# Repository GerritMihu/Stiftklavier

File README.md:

# Stiftklavier / Stylophone

**Ein Open-Source-Lehrprojekt für Mechatronik, Elektronik und Musik** – ideal für Workshops, Schulen und Maker.

*(Abb.: Fertiger Aufbau mit 3D-gedrucktem Gehäuse)*

---
## 🎯 Projektziel
Das Stiftklavier ist ein **praktisches Lehrmittel**, um:
✅ **Löten und Schaltungen** zu üben (Widerstände, ICs, Transistoren)
✅ **Grundlagen der Tonerzeugung** zu verstehen (Oszillatoren, Filter)
✅ **Mechatronik** zu verbinden (Elektronik + 3D-Druck + Mechanik)
✅ **Kreativität** zu fördern (individuelle Gehäuse, Sound-Experimente)

**Zielgruppe**: Student:innen, Lehrende, Elektronik-Enthusiast:innen

---
## 📦 Inhalte dieses Repos
| Ordner/Datei          | Beschreibung                                  |
|-----------------------|-----------------------------------------------|
| [`3D/`](3D/)          | 3D-Modelle für Gehäuse (STL, FreeCAD)         |
| [`bom/`](bom/)        | Stücklisten (BOM) und Bestelllinks           |
| [`cam/`](cam/)        | **Automatisch generierte KiBot-Exporte** (PDF/PNG/3D) |
| [`Stylophone Documentation.md`](Stylophone%20Documentation.md) | **Detaillierte Aufbauanleitung** 🔗 |
| [`Stylophon_1.kicad_sch`](Stylophon_1.kicad_sch) | KiCad-Schaltplan und Platinenlayout |

---
## 🛠️ Loslegen
### 1. Material besorgen
- [Stückliste (BOM)](bom/) mit empfohlenen Händlern.
- **Werkzeuge**: Lötkolben, Multimeter, 3D-Drucker (optional).

### 2. Aufbauen
→ **[Schritt-für-Schritt-Anleitung](Stylophone%20Documentation.md)**

### 3. Erweitern
- Experimentiere mit **anderen Widerständen** für neue Tonleitern.
- Baue ein **MIDI-Interface** ein (Code-Beispiele folgen).

---
## 🔧 CI/CD mit KiBot (KiCad 10 Docker)
Dieses Repo nutzt **[KiBot](https://github.com/INTI-CMNB/KiBot)** in einem **vorkonfigurierten Docker-Container für KiCad 10**, um automatisch:
- **Schaltpläne als PDF** zu exportieren
- **Platinen-Layouts als PNG** zu rendern
- **3D-Ansichten** der Platine zu generieren

👉 **Ergebnisse**: Siehe [`cam/`](cam/)-Ordner (automatisch aktualisiert bei Pushs).

---
## 🤝 Mitwirken
- **Fehler gefunden?** → [Issue erstellen](https://github.com/GerritMihu/Stiftklavier/issues)
- **Verbesserungen?** → Pull Requests willkommen!
- **Fragen?** → Diskussionsbereich nutzen.

---
## 📄 Lizenz
[MIT](LICENSE) – Nutze, modifiziere und teile das Projekt frei!

<!-- KiBot Docker Pipeline Test Trigger: $(date +%s) -->

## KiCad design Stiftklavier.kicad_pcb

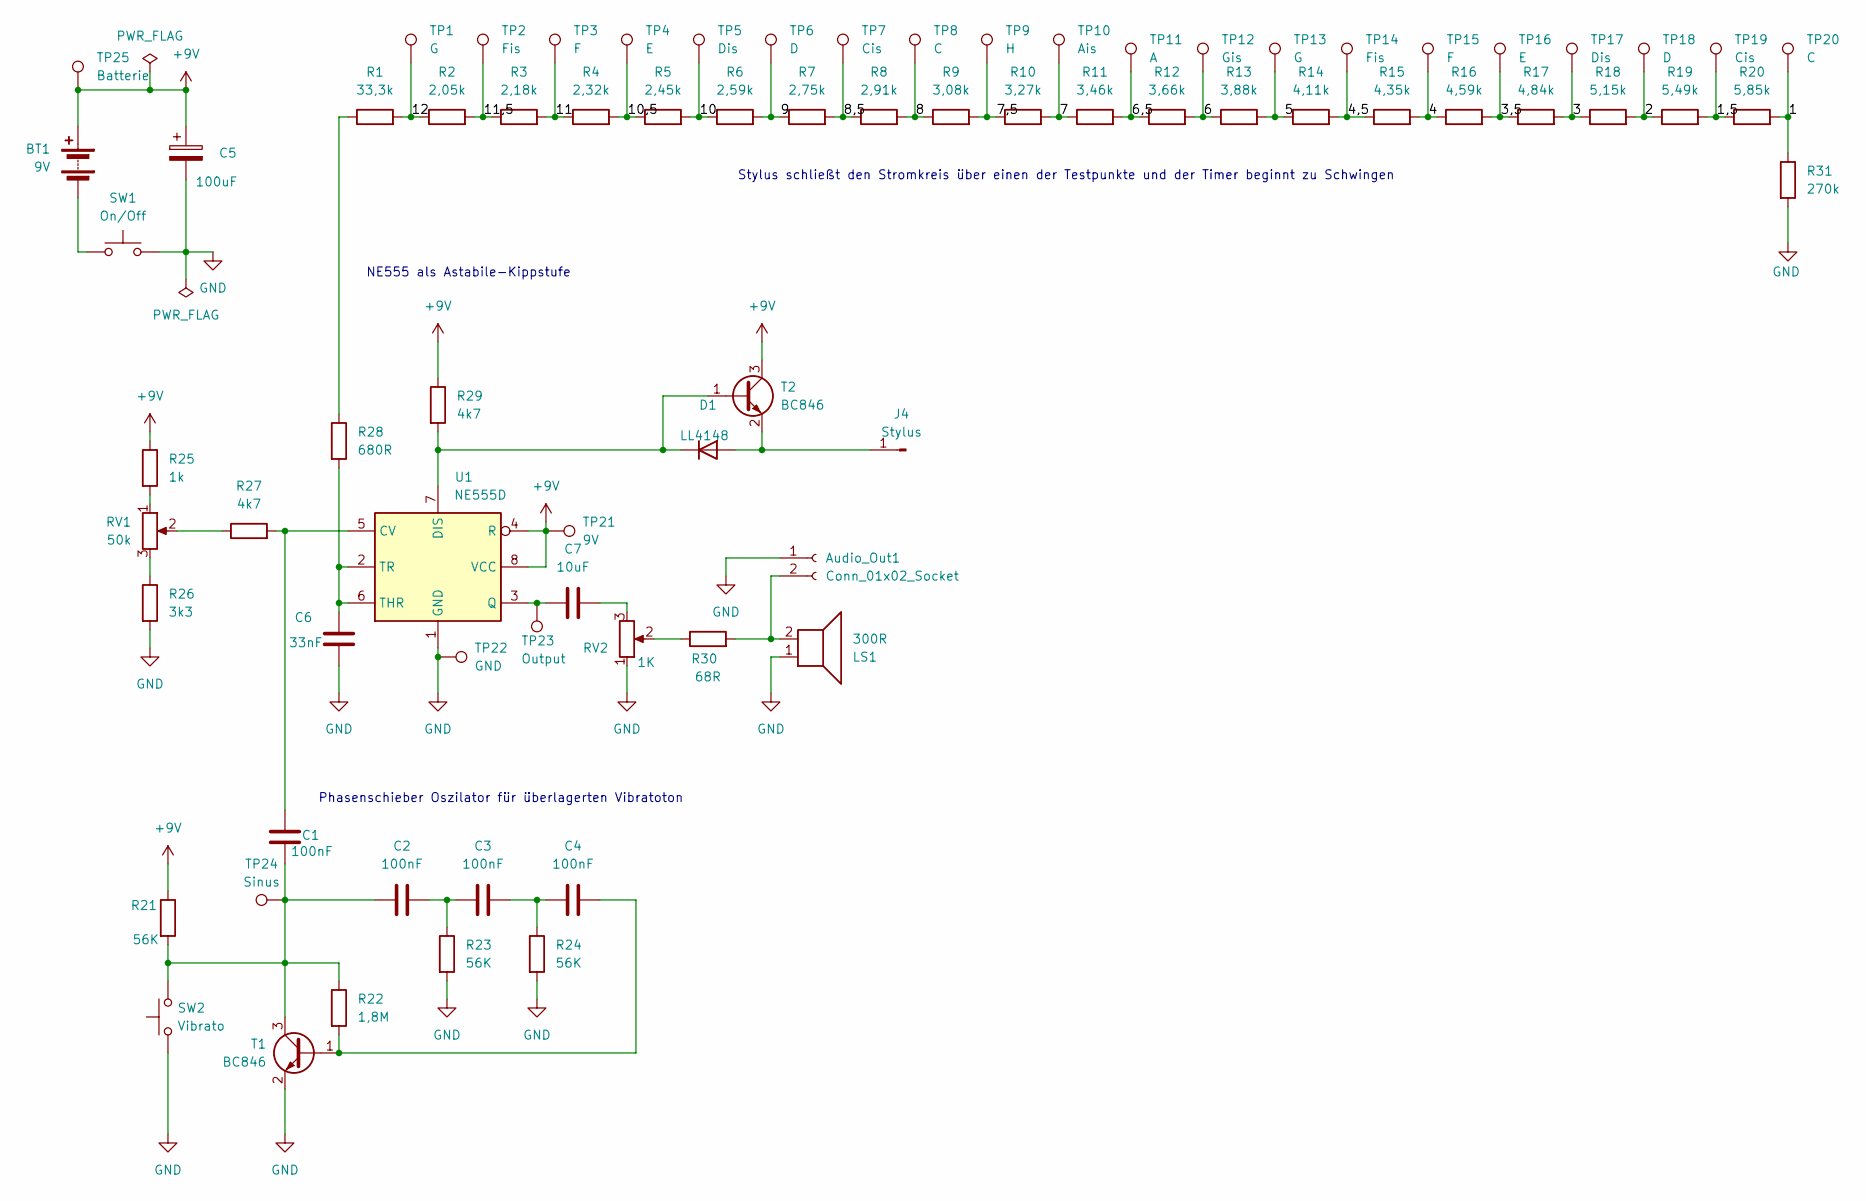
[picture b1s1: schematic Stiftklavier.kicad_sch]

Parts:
Audio_Out1: Conn_01x02_Socket; PinSocket_1x02_P2.00mm_Vertical
BT1: 9V; PinHeader_1x02_P2.54mm_Vertical
C1, C2, C3, C4: 100nF; C_0805_2012Metric_Pad1.18x1.45mm_HandSolder
C5: 100uF; CP_Elec_6.3x7.7
C6: 33nF; C_0805_2012Metric_Pad1.18x1.45mm_HandSolder
C7: 10uF; C_0805_2012Metric_Pad1.18x1.45mm_HandSolder
D1: LL4148; D_MiniMELF
J4: Stylus; PinHeader_1x01_P2.00mm_Vertical
LS1: 300R; PinSocket_1x02_P2.00mm_Vertical
R1: 33,3k; R_1206_3216Metric_Pad1.30x1.75mm_HandSolder
R2: 2,05k; R_1206_3216Metric_Pad1.30x1.75mm_HandSolder
R3: 2,18k; R_1206_3216Metric_Pad1.30x1.75mm_HandSolder
R4: 2,32k; R_1206_3216Metric_Pad1.30x1.75mm_HandSolder
R5: 2,45k; R_1206_3216Metric_Pad1.30x1.75mm_HandSolder
R6: 2,59k; R_1206_3216Metric_Pad1.30x1.75mm_HandSolder
R7: 2,75k; R_1206_3216Metric_Pad1.30x1.75mm_HandSolder
R8: 2,91k; R_1206_3216Metric_Pad1.30x1.75mm_HandSolder
R9: 3,08k; R_1206_3216Metric_Pad1.30x1.75mm_HandSolder
R10: 3,27k; R_1206_3216Metric_Pad1.30x1.75mm_HandSolder
R11: 3,46k; R_1206_3216Metric_Pad1.30x1.75mm_HandSolder
R12: 3,66k; R_1206_3216Metric_Pad1.30x1.75mm_HandSolder
R13: 3,88k; R_1206_3216Metric_Pad1.30x1.75mm_HandSolder
R14: 4,11k; R_1206_3216Metric_Pad1.30x1.75mm_HandSolder
R15: 4,35k; R_1206_3216Metric_Pad1.30x1.75mm_HandSolder
R16: 4,59k; R_1206_3216Metric_Pad1.30x1.75mm_HandSolder
R17: 4,84k; R_1206_3216Metric_Pad1.30x1.75mm_HandSolder
R18: 5,15k; R_1206_3216Metric_Pad1.30x1.75mm_HandSolder
R19: 5,49k; R_1206_3216Metric_Pad1.30x1.75mm_HandSolder
R20: 5,85k; R_1206_3216Metric_Pad1.30x1.75mm_HandSolder
R21, R23, R24: 56K; R_1206_3216Metric_Pad1.30x1.75mm_HandSolder
R22: 1,8M; R_1206_3216Metric_Pad1.30x1.75mm_HandSolder
R25: 1k; R_1206_3216Metric_Pad1.30x1.75mm_HandSolder
R26: 3k3; R_1206_3216Metric_Pad1.30x1.75mm_HandSolder
R27, R29: 4k7; R_1206_3216Metric_Pad1.30x1.75mm_HandSolder
R28: 680R; R_1206_3216Metric_Pad1.30x1.75mm_HandSolder
R30: 68R; R_1206_3216Metric_Pad1.30x1.75mm_HandSolder
R31: 270k; R_1206_3216Metric_Pad1.30x1.75mm_HandSolder
RV1: 50k; PinSocket_1x03_P2.00mm_Vertical
RV2: 1K; PinSocket_1x03_P2.00mm_Vertical
SW1: On/Off; Nidec_Copal_SH-7040B
SW2: Vibrato; Nidec_Copal_SH-7040B
T1, T2: BC846; SOT-23
TP1, TP13: G; Keypad_Right
TP2, TP14: Fis; Keypad_Small
TP3, TP15: F; Keypad_Small
TP4, TP16: E; Keypad_Small
TP5, TP17: Dis; Keypad_Left
TP6, TP18: D; Keypad_Right
TP7, TP19: Cis; Keypad_Small
TP8: C; Keypad_Small
TP9: H; Keypad_Small
TP10: Ais; Keypad_Small
TP11: A; Keypad_Small
TP12: Gis; Keypad_Left
TP20: C; Keypad_Left
TP21: 9V; TestPoint_Pad_D1.5mm
TP22: GND; TestPoint_Pad_D1.5mm
TP23: Output; TestPoint_Pad_D1.5mm
TP24: Sinus; TestPoint_Pad_D1.5mm
TP25: Batterie; TestPoint_Pad_D1.5mm
U1: NE555D; SOIC-8_3.9x4.9mm_P1.27mm

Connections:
+9V: BT1.1 (+), C5.1, R21.1, R25.1, R29.1, T2.3 (C), TP21.1, TP25.1, U1.4 (R), U1.8 (VCC)
/1: R20.2, R31.1, TP20.1
/1,5: R19.2, R20.1, TP19.1
/2: R18.2, R19.1, TP18.1
/3: R17.2, R18.1, TP17.1
/3,5: R16.2, R17.1, TP16.1
/4: R15.2, R16.1, TP15.1
/4,5: R14.2, R15.1, TP14.1
/5: R13.2, R14.1, TP13.1
/6: R12.2, R13.1, TP12.1
/6,5: R11.2, R12.1, TP11.1
/7: R10.2, R11.1, TP10.1
/7,5: R9.2, R10.1, TP9.1
/8: R8.2, R9.1, TP8.1
/8,5: R7.2, R8.1, TP7.1
/9: R6.2, R7.1, TP6.1
/10: R5.2, R6.1, TP5.1
/10,5: R4.2, R5.1, TP4.1
/11: R3.2, R4.1, TP3.1
/11,5: R2.2, R3.1, TP2.1
/12: R1.2, R2.1, TP1.1
GND: Audio_Out1.1, C5.2, C6.2, LS1.1, R23.2, R24.2, R26.2, R31.2, RV2.1, SW1.2, SW2.1, T1.2 (E), TP22.1, U1.1 (GND)
unnamed: Audio_Out1.2, LS1.2, R30.2
unnamed: BT1.2 (-), SW1.1
unnamed: C2.1, C3.2, R23.1
unnamed: C3.1, C4.2, R24.1
unnamed: C7.2, RV2.3
unnamed: D1.2 (A), J4.1, T2.2 (E)
unnamed: D1.1 (K), R29.2, T2.1 (B), U1.7 (DIS)
unnamed: R1.1, R28.1
unnamed: R25.2, RV1.1
unnamed: R26.1, RV1.3
unnamed: R27.1, RV1.2
unnamed: R30.1, RV2.2
unnamed: C4.1, R22.2, T1.1 (B)
unnamed: C1.1, C2.2, R21.2, R22.1, SW2.2, T1.3 (C), TP24.1
unnamed: C1.2, R27.2, U1.5 (CV)
unnamed: C7.1, TP23.1, U1.3 (Q)
unnamed: C6.1, R28.2, U1.2 (TR), U1.6 (THR)

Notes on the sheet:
Phasenschieber Oszilator für überlagerten Vibratoton
NE555 als Astabile-Kippstufe
Stylus schließt den Stromkreis über einen der Testpunkte und der Timer beginnt zu Schwingen

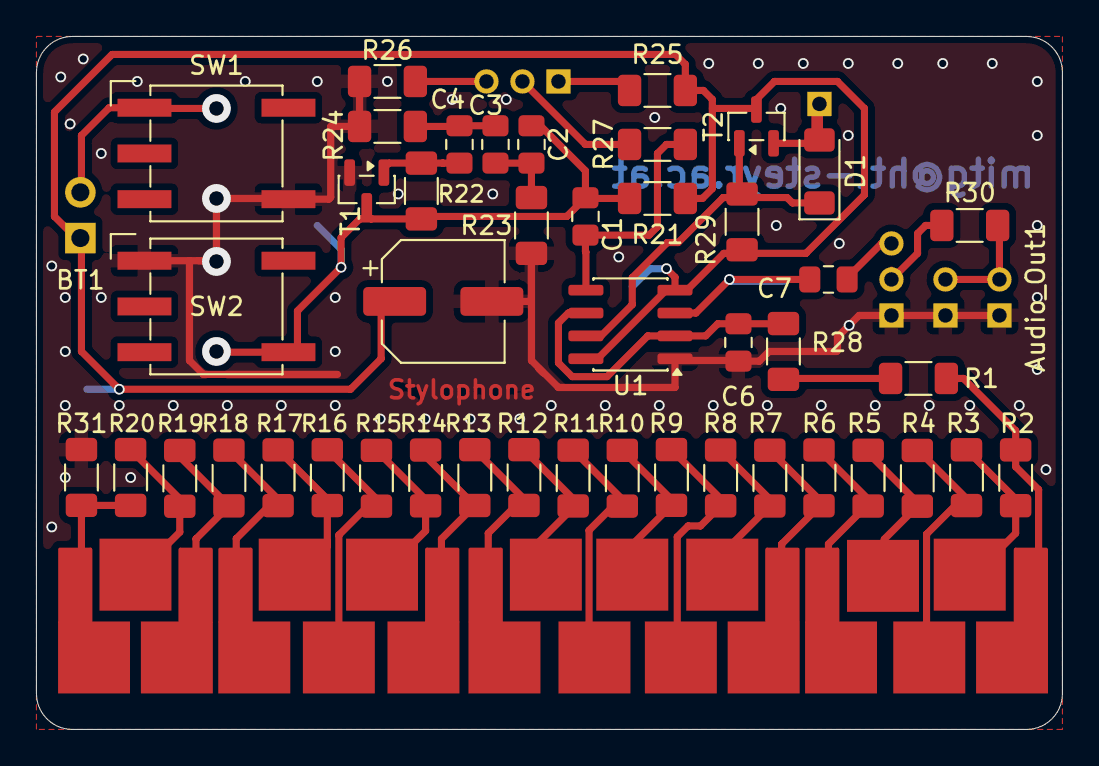
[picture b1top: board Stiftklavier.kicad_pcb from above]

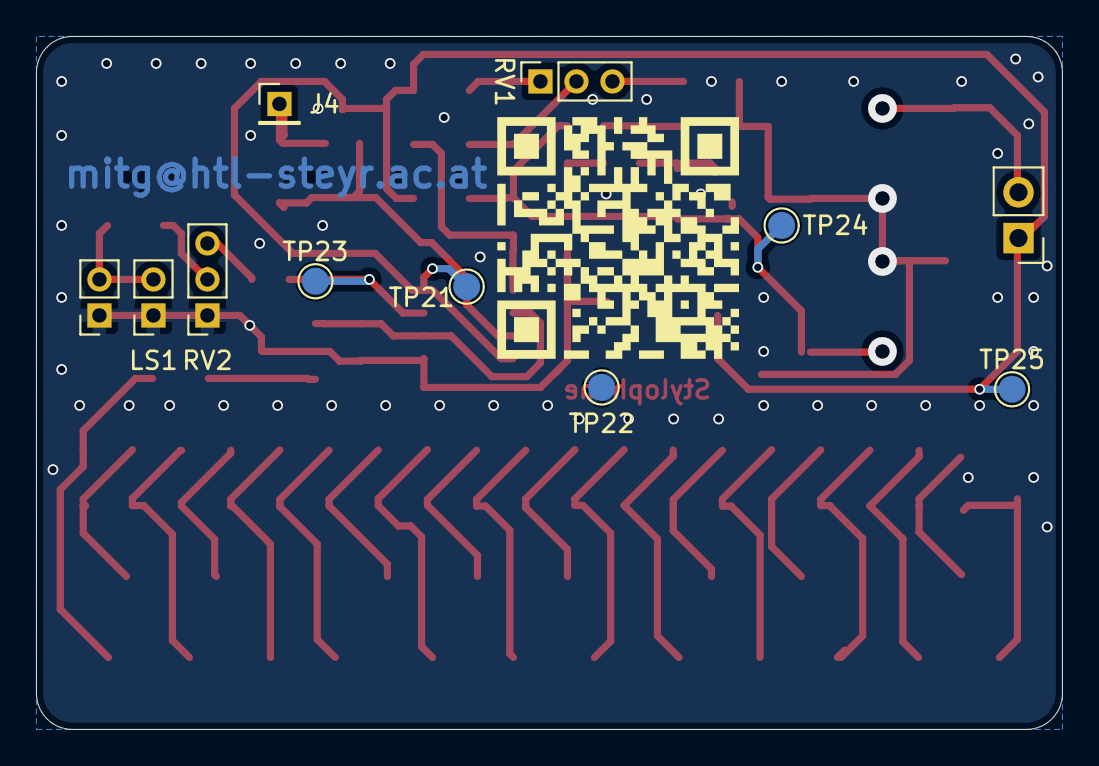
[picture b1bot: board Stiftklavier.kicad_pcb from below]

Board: 2 copper layers, 57.0 x 38.5 mm, 75 parts (11 on the bottom side), 39 nets.

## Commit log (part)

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2024-04-03 Add Files
2024-12-23 Doku verbessert
    von Fr. Großalber
2024-12-23 added directories for better organisation
2024-12-23 added case
2025-09-07 Updated Component Values
2025-09-07 PCB updated
2025-09-07 Added keys like a real one
2025-09-07 VIA stitching & GND Plane QR
2025-09-07 title
2025-12-15 gerber/dxf
2026-03-23 Keyboard improvement
2026-03-23 Release V1.0
2026-04-06 Add KiBot CI/CD workflow for automatic schematic/PCB exports
2026-04-06 Add KiBot configuration for schematic, PCB and 3D exports
2026-04-06 Add comprehensive build guide with step-by-step instructions, warnings, and troubleshooting
2026-04-06 Update build guide: comprehensive step-by-step instructions, warnings, and troubleshooting
2026-04-06 Update KiBot workflow for KiCad 10 compatibility
2026-04-06 Update KiBot config for KiCad 10 project file support
2026-04-06 Update README to reflect KiCad 10 and KiBot pipeline
2026-04-06 Trigger KiBot pipeline test
2026-04-06 Fix KiBot installation with --no-compile for KiCad 10 compatibility
2026-04-06 Trigger KiBot pipeline with updated README
2026-04-08 Update to KiBot Docker container for KiCad 10
2026-04-08 Trigger KiBot Docker pipeline with updated README timestamp
2026-05-04 Name correction
2026-05-04 Rename generate new gerber
